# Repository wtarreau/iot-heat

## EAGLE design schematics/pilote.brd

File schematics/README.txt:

The circuit is purpusely single sided, with all the generic stuff under the
ESP and the project-specific one around, so that adapting it to any other use
case should be easy. Particular care was given to make the default circuit
entirely fit under the ESP so that a programming board could be made to use in
sandwich between the ESP and any other board, with only the programming
connector being available. Less than 0.2mm are left spare between some pads
and some tracks, and tracks are as small as 0.254mm. Engraving and etching
must have a fine precision.

The programming is made using the GPIO and EN pin so that GPIO16 can still be
used with RESET to keep the watchdog operational.

Any classical USB-TTL adapter with the R/C pin configured to send RTS will
work. Most CH340-based ones are configurable. Some FTDI-based adapters
are also compatible. The circuit requires to operate under 3V and provided
by the adapter. It automatically resets the board when asserting RTS, which
is what esptool does when it flashes a firmware image.

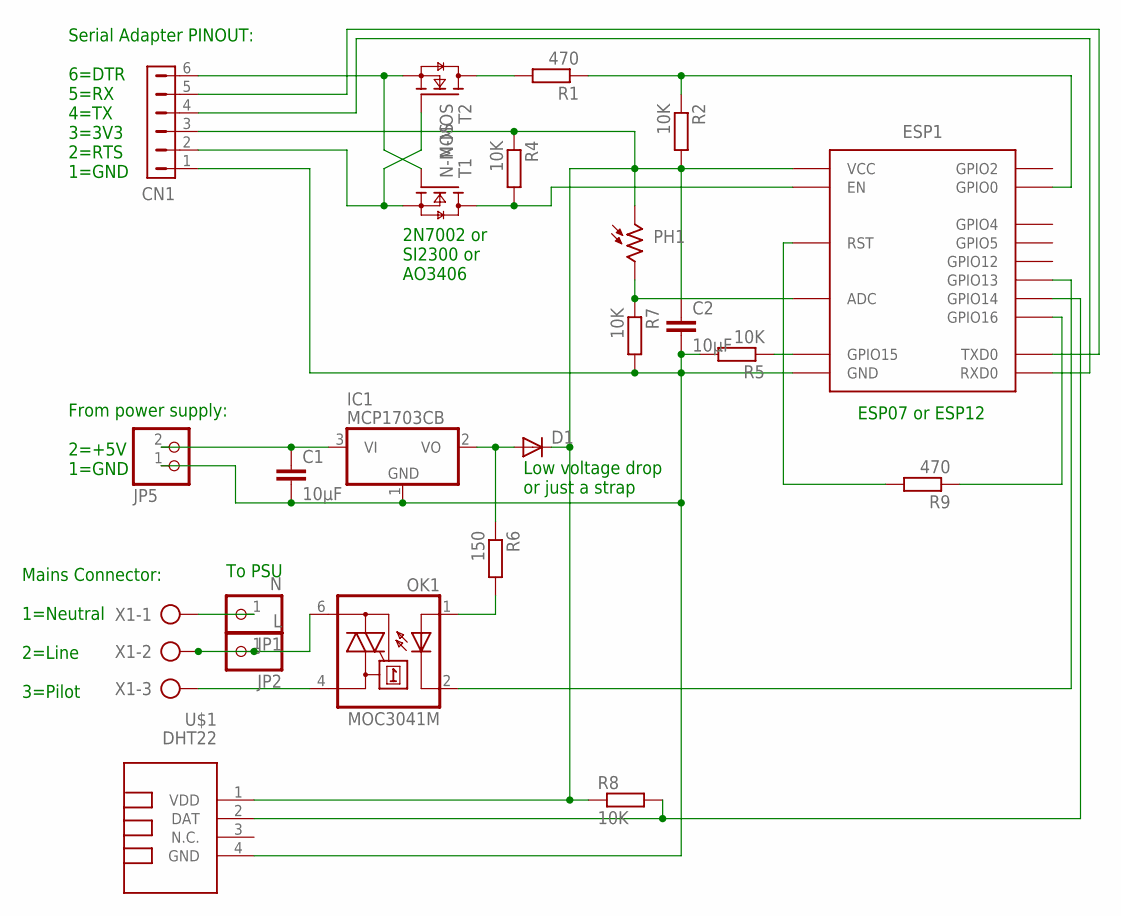
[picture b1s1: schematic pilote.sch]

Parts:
C1, C2: 10µF; C1210
CN1: HDR-1X6-SIP-100; SIP-100-6V
D1: DIODE-SOD123; SOD123
ESP1: ESP8266-07THT; ESP-07
IC1: MCP1703CB; SOT23
JP1: N; 1X01
JP2: L; 1X01
JP5: PINHD-1X2; 1X02
OK1: MOC3041M; DIL06
PH1: A1050_09; T0-46-A10XX
R1, R9: 470; M0805
R2, R4, R5, R7, R8: 10K; M0805
R6: 150; M0805
T1, T2: N-MOS; SOT23
U$1: DHT22; TEMP-HUM-SENSOR-DHT22
X1: AK500/3

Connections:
unnamed: ESP1.ADC, PH1.2, R7.1
unnamed: CN1.2, T1.1 (G), T2.2 (S)
unnamed: CN1.6, T1.2 (S), T2.1 (G)
unnamed: OK1.4 (A1), X1.3
unnamed: R1.2, T1.3 (D)
unnamed: ESP1.GPIO0, R1.1, R2.1
unnamed: C2.1, CN1.3, D1.C, ESP1.VCC, PH1.1, R2.2, R4.1, R8.1, U$1.1 (VDD)
unnamed: JP1.1, X1.1
unnamed: ESP1.EN, R4.2, T2.3 (D)
unnamed: ESP1.RST, R9.2
unnamed: ESP1.GPIO15, R5.1
unnamed: C1.1, IC1.3 (VI), JP5.2
unnamed: C1.2, C2.2, CN1.1, ESP1.GND, IC1.1 (GND), JP5.1, R5.2, R7.2, U$1.4 (GND)
unnamed: OK1.1 (A), R6.2
unnamed: JP2.1, OK1.6 (A2), X1.2
unnamed: CN1.4, ESP1.RX (RXD0)
unnamed: ESP1.GPIO13, OK1.2 (C)
unnamed: CN1.5, ESP1.TX (TXD0)
unnamed: ESP1.GPIO14, R8.2, U$1.2 (DAT)
unnamed: ESP1.GPIO16, R9.1
unnamed: D1.A, IC1.2 (VO), R6.1

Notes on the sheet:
Serial Adapter PINOUT: 6=DTR 5=RX 4=TX 3=3V3 2=RTS 1=GND
From power supply: 2=+5V 1=GND
Mains Connector: 1=Neutral 2=Line 3=Pilot
To PSU
Low voltage drop or just a strap
ESP07 or ESP12
2N7002 or SI2300 or AO3406

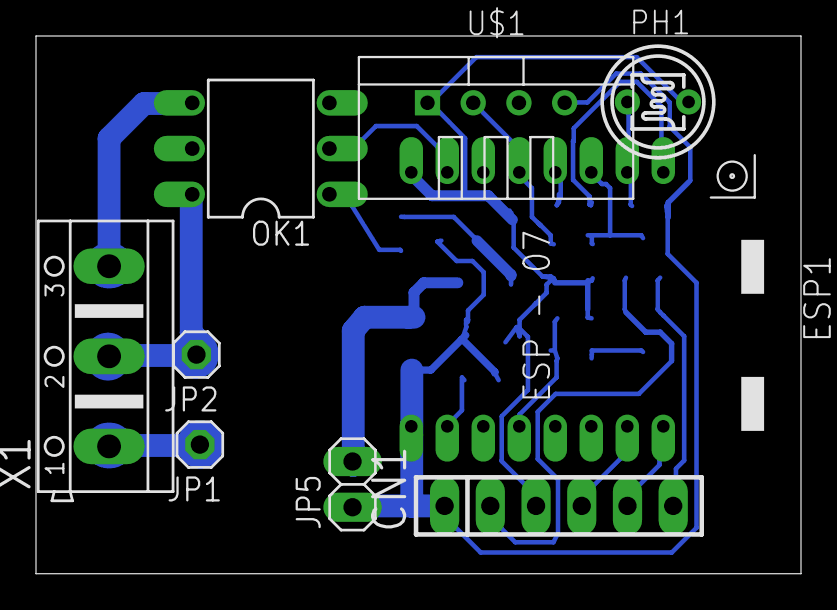
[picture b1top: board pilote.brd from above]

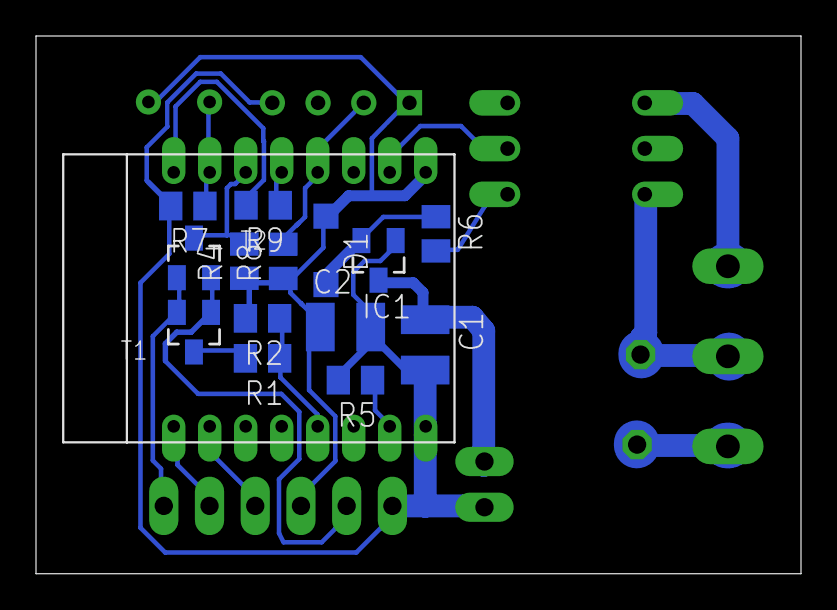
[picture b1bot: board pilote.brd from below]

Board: 2 copper layers, 42.5 x 29.9 mm, 23 parts (14 on the bottom side), 21 nets.

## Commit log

2019-01-13 code: heat: publish temperature and humidity readings
    We implement the read cache and publish the changes over MQTT
    as humi_cur (percent between 0.0 and 100.0) and temp_cur (float
    as well, in celsius).
2019-01-13 code: heat: implement the PWM setting on subscription
    Now we also set the heat_pwm_day and heat_pwm_night variables when
    receiving them, and we use them to dynamically update the PWM output
    on each timer call.
2019-01-13 code: add mqtt-mirror
    This is a simple shell script which maintains a filesystem mirror of
    all MQTT topics known on the server. It's convenient to run shell
    scripts that rely on these values.
2019-01-13 code: heat: add a new application to manage heating devices
    This application connects over MQTT and publishes a few values, for
    now only the measurement of the light sensor to detect people's presence.
    It also subscribes to some topics to get PWM values to be used during day
    and night, as well as an optional change in the limit between day and night.
    For now it checks these elements every second as it's easier for debugging,
    but the frequency could be arranged and a cache could be used for unchanged
2019-01-13 code: heat: change default light threshold
    On the new version of the design, the light sensor spans a much wider
    range and detects light through the plastic. Lower the threshold to
    100 to detect between night and day.
2019-01-13 code: heat: implement automatic reconnection after an error
    The MQTT connect() immediately fails when started before the network
    is ready, and doesn't retry. For this reason we implement automatic
    reconnection when trying to send a message in the update timer. We
    now maintain 3 states : disconnected(0), connecting(1), connected(2).
    Any publication will automatically lead to an attempt to reconnect.
2019-01-13 doc: heat: add new states do describe periods of the day
    We now have 8 states :
    NIGHT, WAKEUP, MORNING, ATHOME,
    AWAY, BACK, EVENING, TOBED
    For each of them a profile will be applied for light and darkness.
    Each of these profiles will correspond to a heating offset.
2019-01-13 code: heat: make the light reading function update the global value
    Better have sensors automatically update the current value, as
    we'll have to take into account the operation success for some
    of them.
2019-01-13 code: heat: implement a cache of MQTT publications
    The principle is not to resubmit values which have not changed, as is
    the case for most constants and thresholds.
2019-01-13 code: heat: now also read the temperature and humidity in the loop
    For this we read the DHT22 sensor and update the respective global
    variables (heat_temp_cur and heat_humi_cur).
2019-01-13 code: heat: remove the code used to manipulate gpio for adc
    The prototype used to employ two analog devices multiplexed using GPIO.
    These ones don't exist anymore, remove this code.
2019-01-13 code: add a new script "mqtt-heating" for the controller
    This one sets some "environment" variables, the most important one
    being "state" to indicate what state the house is in among 8 possible.
    It collects the light from a few online nodes and has some preset
    time boundaries. It's very experimental for now.
2019-01-13 code: heat: add support for a config file to set the profile
    The new file cfg/heat-cfg.lua will be sourced if it exists. It will
    be used to set the various PWM levels for all 4 profiles, and the
    profiles to be used for each combination of state,light.
2019-01-13 code: heat-cfg: provide example heat config file for a living room
    This is for a living room, in short, STRONG heating in the morning,
    ECO mode when away, NORMAL heating when there's light, ECO for the
    rest.
2019-01-13 code: heat: retrieve the current state from the environment
    The central controller is supposed to be running mqtt-heating to update
    the environment based on the time of day and a collection of lights from
    various nodes. For now it's not used.
2019-01-13 code: heat: increase the temperature offset by 10% when humidity > 70%
    This is in order to improve comfort. It's done on a per-heater basis.
2019-01-13 code: heat: now take the heating profile into account for the PWM
    The moment of the day is retrieved from MQTT and combined with the
    light detection to give the current heating profile. This heating
    profile is then converted to PWM.
    The FAST mode is not implemented for now.
2019-01-13 code: heat: support fast heating when leaving ECO mode
    When leaving ECO mode, we switch to FAST state for at most as long as
    we were in ECO mode, limited to 1000 seconds. One of the limits is that
    if the heater is turned on cold without going to ECO mode, we don't
    know how to turn it to FAST mode. If we did it it would cause the heater
    to be set to full throttle upon each turn on, which is not desirable.
2019-01-13 MINOR: heat: allow more transitions to BACK
    for example it was not possible to enter it at night or during the day.
2019-01-13 code: mqtt-heating: add a transition from evening to morning
    This is for when "tobed" was not performed whatever the reason.
    Also some time checks were improved because some 'ge' and 'lt'
    are insufficient given that they're here to imply "after" but
    don't take into account to wrapping of time. There are still a
    lot to fix.
2019-01-13 MINOR: heat: support touching /tmp/returning to set BACK
    It should be changed to allow to force any state.
2019-01-13 code: mqtt-heating: earlier wake-up
    Let's use 3h30 pre-heat and 5h30 leave time.
2019-01-13 conf: add sample configurations
    These ones show how to quickly configure the mqtt server and the network.
2019-01-13 code: add board.lua
    This sets the I/O pins used in the project, though most are hard-coded,
    but at least the recovery button allows to get back to a shell in case
    of problem.
2019-01-13 doc: indicate the flashing procedure
    It's very similar to the other projects' but focuses on the extra care
    required for the config file.
2019-01-13 doc: add a diagram explaining the architecture
    This shows how the heaters and central controller communicate via the
    MQTT server.
2019-01-13 doc: add minimal documentation about the daemons and their configuration
    The doc is very succint but helpful for later modifications.
2019-01-13 doc: add a photo of the final assembly
    This helps identifying how to place most components.
2019-01-22 code: mqtt-heating: support sending an e-mail alert
    The code may stop working because of network errors for example. In
    this case, provide the option to send an e-mail alert before quitting.
2020-02-03 doc: mention start.lua for newer iot-core
    The last iot-core split init into init+start, let's reflect this in the
    flashing procedure.
2020-02-03 code: make the DHT pin configurable
    It's now brd_dht and not the hard-coded value "4" for GPIO2.
2020-02-03 code: make the PWM pin configurable
    No need for this one to be hard-coded either.
2020-02-03 conf: move board.lua from code to conf
    It's mostly a matter of board configuration and variations may occur
    depending on the module in use, so make this pure config and not code.
2020-02-03 conf: move heat-cfg.lua to the conf directory
    This one may also change based on board variations (e.g. PWM values) so
    it definitely is config more than code.
2020-02-03 code: make the onboard led blink to reflect activity and mode
    During each call to the timer, we'll blink the onboard led if it is
    defined (brd_led, brd_led_inv). In ECO mode, the led is off by default
    and flashes on. In other modes, the led is on by default and flashes
    off. Note that the onboard LED on ESP12E and newer is connected to
    GPIO2 (D4) which is also the pin that was used to connect the DHT
    module on some boards.
2020-02-03 conf: add a variant for Pilot Wire
    This variant connects a MOC3041 triac to the PWM output which is then
    used in full-on, full-off mode. It would be interesting to see if by
    modulating it at 50 Hz and using a half-wave ratio it's possible to
    switch to the -1 or -2 degrees that some devices support, or if this
    requires phase synchronization.
2020-02-03 code: remove unused heat_pwm_day and heat_pwm_night variables
    These ones were learned over MQTT but never used. Let's remove them.
2020-02-03 code: change the PWM speed without a setup phase
    Doing a setup()+start() cycle every second causes short pulses on output
    that are noticeable, especially when no signal should be emitted. Instead
    let's use a setup() phase and a write() phase which remains synchronous.
2020-02-03 schematic: add the schematic, board and corresponding images
    This will ease duplicating the device. The circuit is purpusely single
    sided, with all the generic stuff under the ESP and the project-specific
    one around, so that adapting it to any other use case should be easy.
    Particular care was given to make the default circuit entirely fit under
    the ESP so that a programming board could be made to use in sandwich
    between the ESP and any other board, with only the programming connector
2020-02-03 photos: add photos of various stages of the realization
    These may also be useful to try to diagnose malfunction.
2020-04-08 code: add node 8403863 to meaningful light sensors
    This node will report a valid light state now.
2020-11-16 code: add missing transition from NIGHT when lights > 0
    If the program was restarted in the evening, no transition existed to
    consider the light state and the only way was to touch /tmp/returning
    which is a remote alternative to local lights. This patch implements
    the equivalent transitions conditioned by light detection.
2021-02-10 code: fix never-ending TOBED state
    Commit 7ff5c48 ("code: add missing transition from NIGHT when lights > 0")
    introduced missing transitions but that resulted in the TOBED state to be
    almost impossible to leave. It appears to require the same transitions as
    the NIGHT state, each with an extra transition between each other depending
    on the light state. Let's just merge the two states in the code and add
    the missing transition.

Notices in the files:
parts and their libraries:
con-hdrs40: Copyright (C) 2004, Bob Starr (bobstarr@mindspring.com)
diy-modules: Released under the Creative Commons Attribution 4.0 International License: http://creativecommons.org/licenses/by/4.0
